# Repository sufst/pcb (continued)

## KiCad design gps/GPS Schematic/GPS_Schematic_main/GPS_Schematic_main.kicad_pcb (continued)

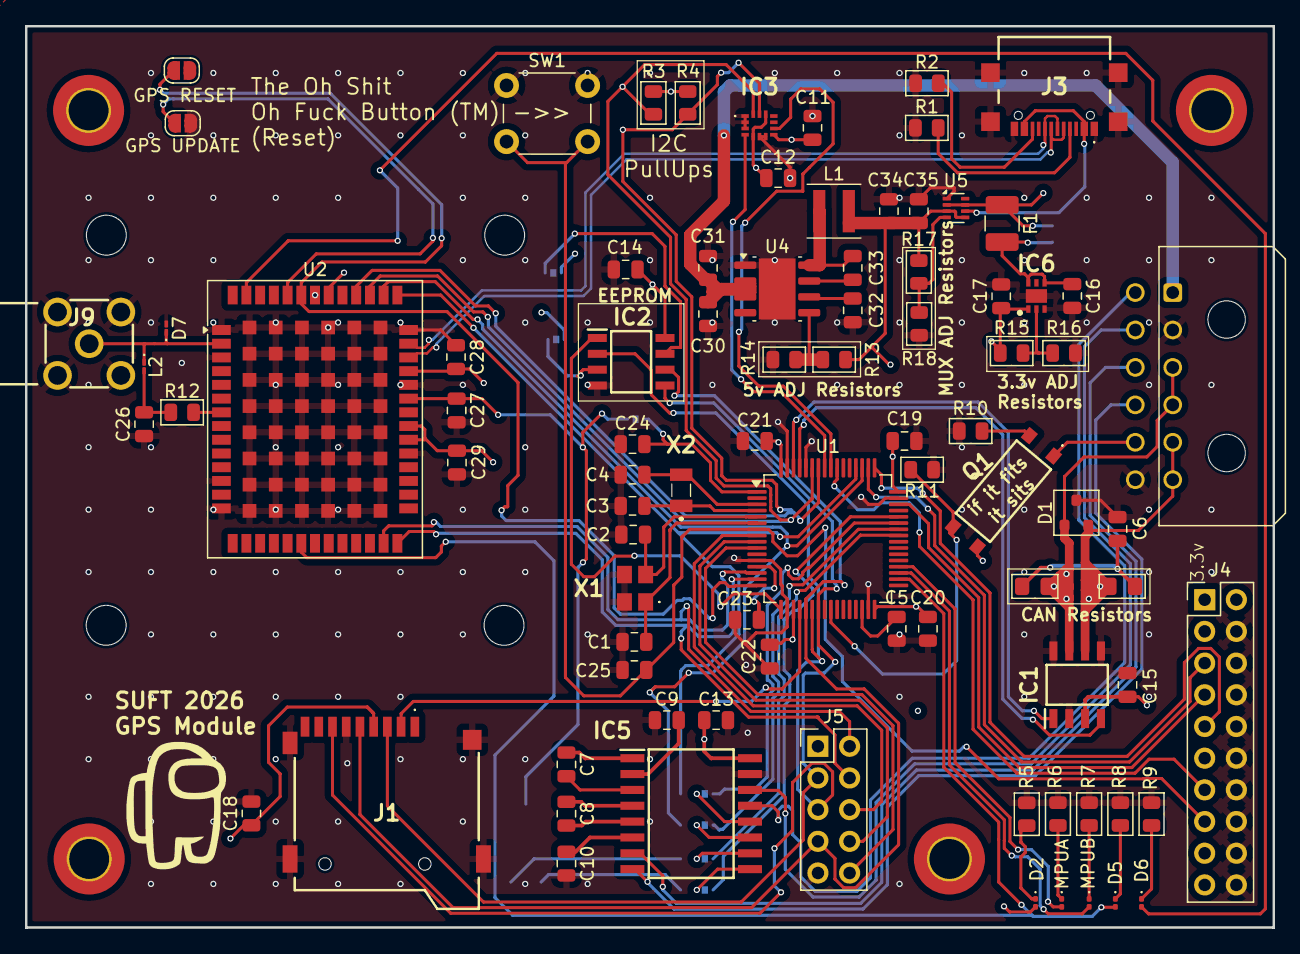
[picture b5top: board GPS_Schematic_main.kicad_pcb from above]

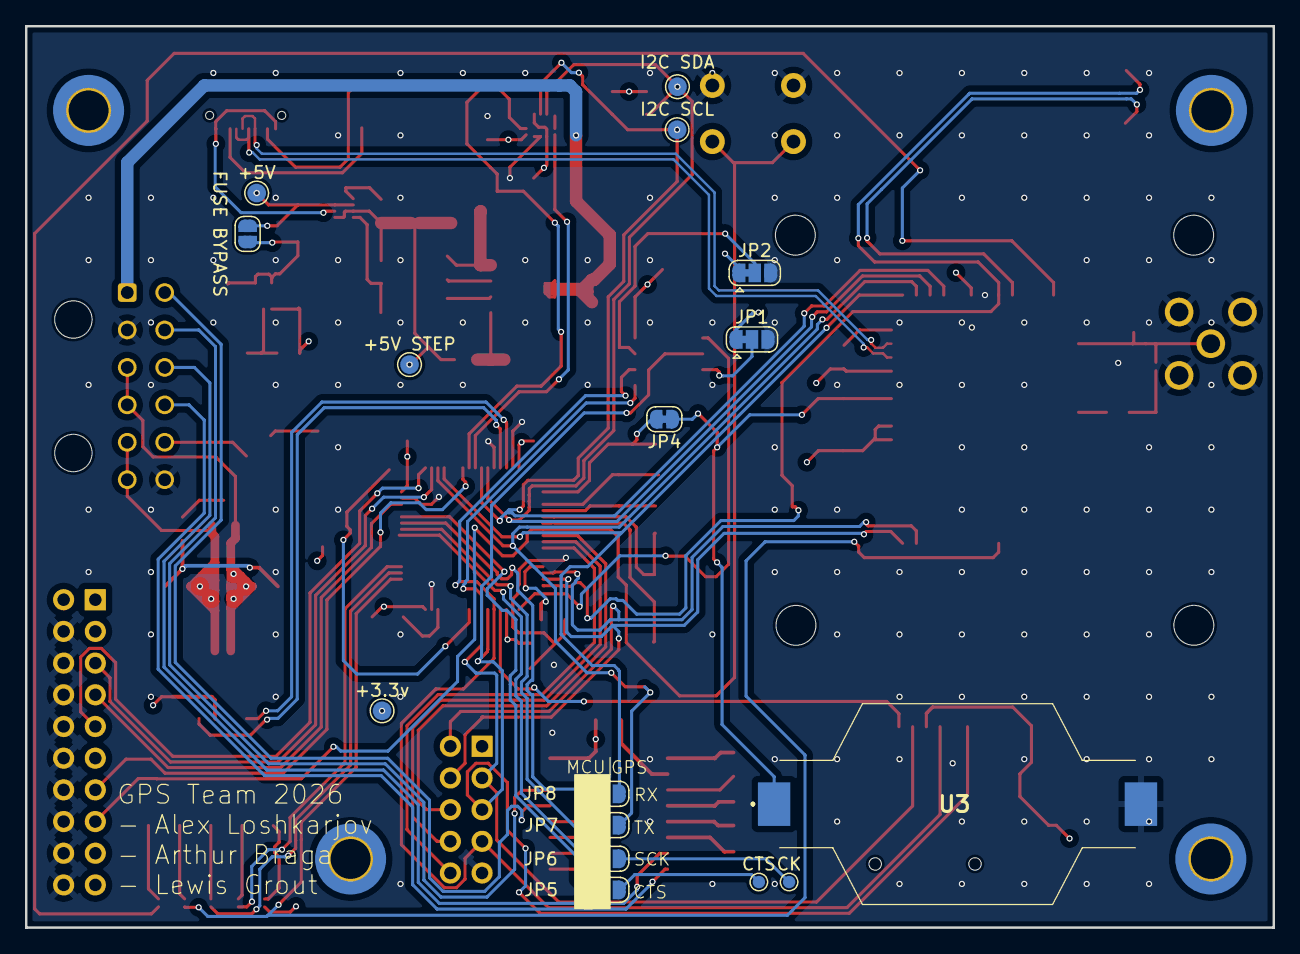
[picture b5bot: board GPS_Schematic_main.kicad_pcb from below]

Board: 4 copper layers, 100.0 x 72.2 mm, 102 parts (16 on the bottom side), 89 nets.

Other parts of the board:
+3.3v, +5V, +5V STEP: TestPoint; TestPoint_Pad_D1.5mm
CK: CK; TestPoint_Pad_D1.0mm
CTS: CTS; TestPoint_Pad_D1.0mm
FUSE BYPASS: FUSE BYPASS; SolderJumper-2_P1.3mm_Open_RoundedPad1.0x1.5mm
GPS RESET: SolderJumper_2_Open; SolderJumper-2_P1.3mm_Open_RoundedPad1.0x1.5mm
GPS UPDATE: SolderJumper_2_Open; SolderJumper-2_P1.3mm_Open_RoundedPad1.0x1.5mm
I2C SCL, I2C SDA: TestPoint; TestPoint_Pad_D1.5mm

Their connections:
+3.3V: +3.3v.1; also elsewhere on the board
+5V: +5V.1, FUSE BYPASS.1 (A); also elsewhere on the board
+5V StepDown: +5V STEP.1; also elsewhere on the board
GND: GPS UPDATE.1 (A); also elsewhere on the board
GPS_NRST: GPS RESET.2 (B); also elsewhere on the board
I2C_SCL: I2C SCL.1; also elsewhere on the board
I2C_SDA: I2C SDA.1; also elsewhere on the board
unnamed 45: GPS UPDATE.2 (B); also elsewhere on the board
unnamed 58: FUSE BYPASS.2 (B); also elsewhere on the board
unnamed 63: CTS.1; also elsewhere on the board
unnamed 64: CK.1; also elsewhere on the board

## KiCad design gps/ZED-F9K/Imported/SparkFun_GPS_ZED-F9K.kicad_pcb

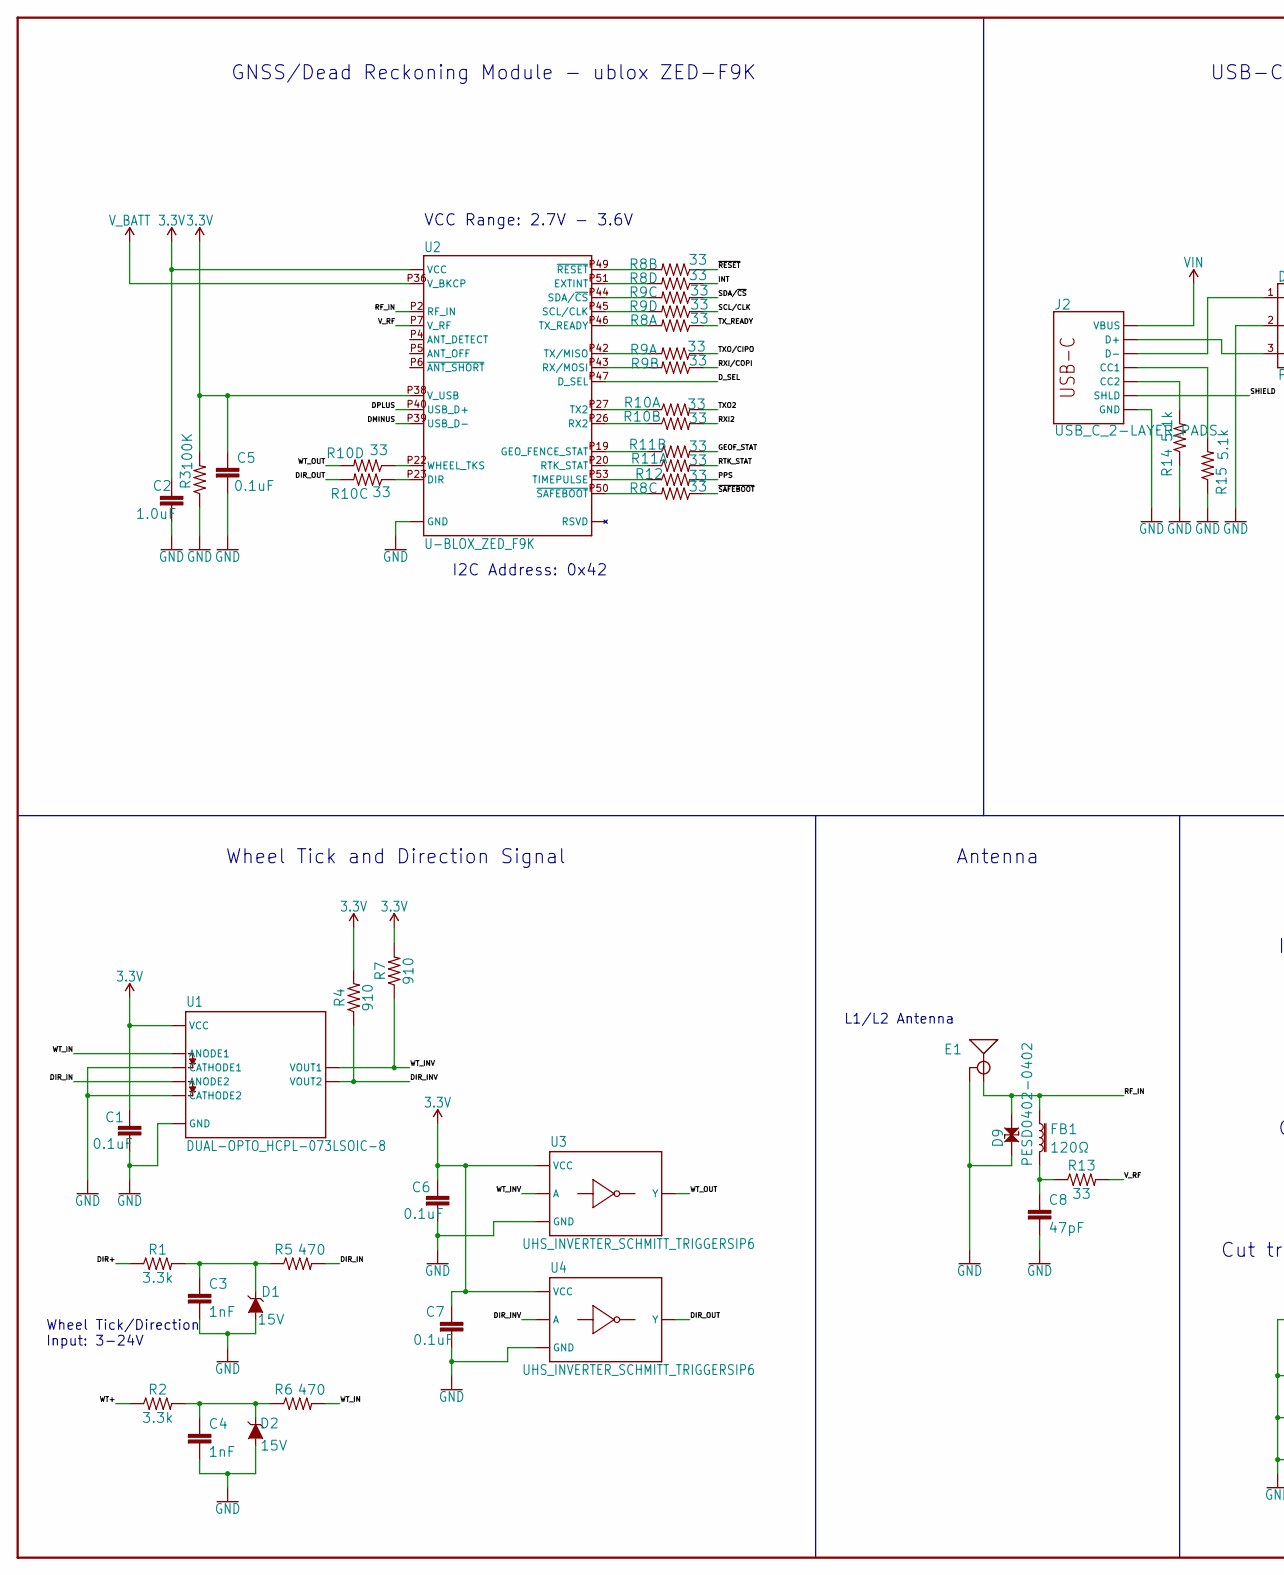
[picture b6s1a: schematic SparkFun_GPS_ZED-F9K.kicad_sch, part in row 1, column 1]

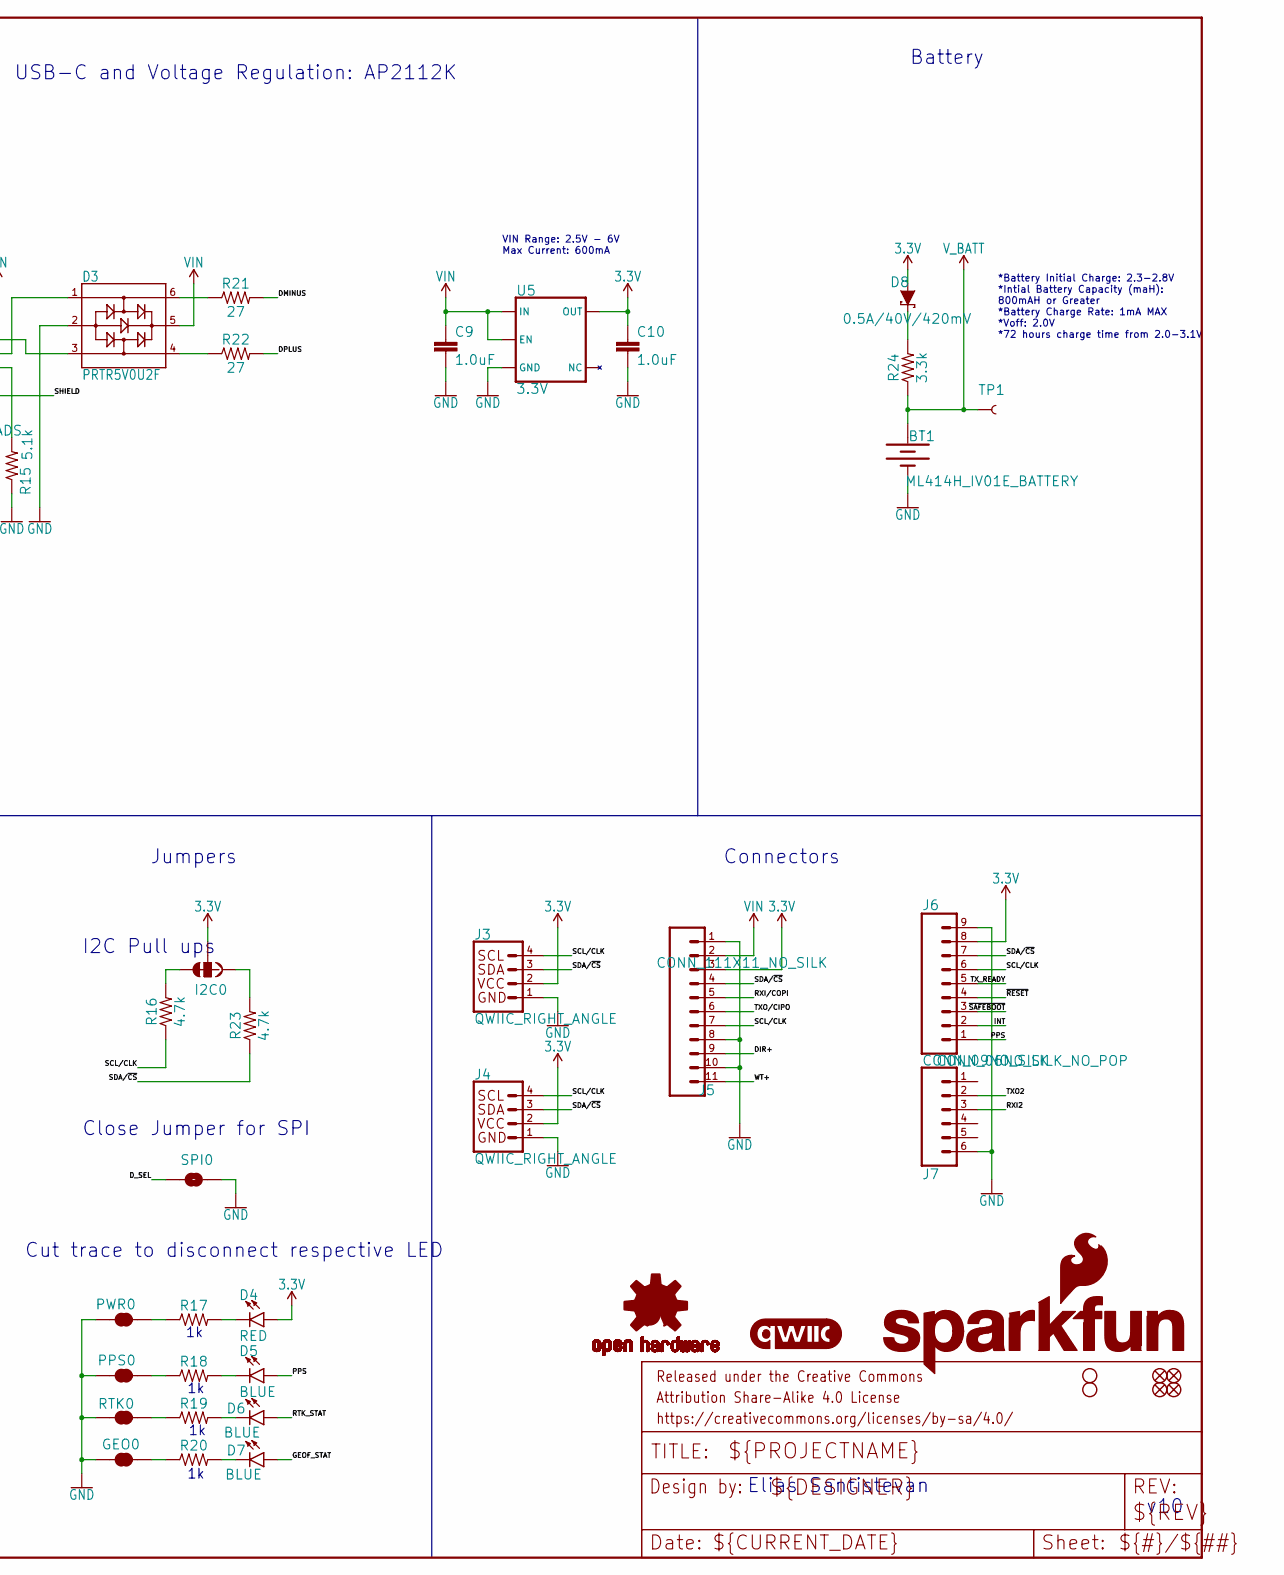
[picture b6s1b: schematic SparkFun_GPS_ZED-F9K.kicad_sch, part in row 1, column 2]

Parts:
$1_25_$_2020-03-30_22-52-05: STAND-OFFTIGHT; STAND-OFF-TIGHT
BT1: ML414H_IV01E_BATTERY; ML414H_IV01E
C1, C5, C6, C7: 0.1uF; 0402-TIGHT
C2, C9, C10: 1.0uF; 0402-TIGHT
C3, C4: 1nF; 0402
C8: 47pF; 0402
D1, D2: 15V; SOT23-3
D3: PRTR5V0U2F; SOT886
D4: RED; LED-0603
D5, D6, D7: BLUE; LED-0603
D8: 0.5A/40V/420mV; SOD-323
D9: PESD0402-0402; 0402
E1: ANTENNA-SMA-GROUNDEDEDGE_SMA; SMA-EDGE
FB1: 120Ω; 0402
FD1, FD2, FD3, FD4: FIDUCIALUFIDUCIAL; FIDUCIAL-MICRO
FRAME1: FRAME-LEDGER; CREATIVE_COMMONS
GEO0: JUMPER-SMT_2_NC_TRACE_SILK; SMT-JUMPER_2_NC_TRACE_SILK
H2: STAND-OFFTIGHT; STAND-OFF-TIGHT
I2C0: JUMPER-SMT_3_2-NC_TRACE_SILK; SMT-JUMPER_3_2-NC_TRACE_SILK
J2: USB_C_2-LAYER_PADS; USB-C-16P-2LAYER-PADS
J3, J4: QWIIC_RIGHT_ANGLE; JST04_1MM_RA
J5: CONN_111X11_NO_SILK; 1X11_NO_SILK
J6: CONN_09NO_SILK; 1X09_NO_SILK
J7: CONN_06NO_SILK_NO_POP; 1X06_NO_SILK
LOGO1: OSHW-LOGOS; OSHW-LOGO-S
LOGO2: QWIIC_LOGO_4MM; QWIIC_4MM
LOGO3: SFE_LOGO_NAME_FLAME.2_INCH; SFE_LOGO_NAME_FLAME_.2
PPS0: JUMPER-SMT_2_NC_TRACE_SILK; SMT-JUMPER_2_NC_TRACE_SILK
PWR0: JUMPER-SMT_2_NC_TRACE_SILK; SMT-JUMPER_2_NC_TRACE_SILK
R1, R2, R24: 3.3k; 0603
R3: 100K; 0402
R4, R7: 910; 0603
R5, R6: 470; 0603
R8, R9, R10, R11: 33; 1206_RA
R12, R13: 33; 0603
R14, R15: 5.1k; 0402
R16, R23: 4.7k; 0402-TIGHT
R17, R18, R19, R20: 1KOHM-0402-1/16W-1%; 0402
R21, R22: 27; 0603
RTK0: JUMPER-SMT_2_NC_TRACE_SILK; SMT-JUMPER_2_NC_TRACE_SILK
SPI0: JUMPER-SMT_2_NO_SILK; SMT-JUMPER_2_NO_SILK
TP1: TEST-POINT3X5; PAD.03X.05
U1: DUAL-OPTO_HCPL-073LSOIC-8; SO08
U2: U-BLOX_ZED_F9K; UBLOX_ZED_F9K
U3, U4: UHS_INVERTER_SCHMITT_TRIGGERSIP6; SIP6
U5: 3.3V; SOT23-5

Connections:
3.3V: C1.1, C2.1, C5.1, C6.1, C7.1, C10.1, D4.A, D8.A, I2C0.2, J3.2, J4.2, J5.3, J6.8, R3.2, R4.2, R7.2, U1.8 (VCC), U2.P33 (VCC), U2.P34 (VCC), U2.P38 (V_USB), U3.P6 (VCC), U4.P6 (VCC), U5.5 (OUT)
DIR+: J5.9, R1.1
DIR_IN: R5.2, U1.4 (ANODE2)
DIR_INV: R4.1, U1.6 (VOUT2), U4.P2 (A)
DIR_OUT: R10.P6 (2), U4.P4 (Y)
DMINUS: R21.2, U2.P39 (USB_D-)
DPLUS: R22.2, U2.P40 (USB_D+)
D_SEL: SPI0.1, U2.P47 (D_SEL)
GEOF_STAT: D7.A, R11.P7 (2)
GND: BT1.-, C1.2, C2.2, C3.2, C4.2, C5.2, C6.2, C7.2, C8.2, C9.2, C10.2, D1.1 (A), D2.1 (A), D3.2, D9.1, E1.GND@0 (GND), E1.GND@1 (GND), E1.GND@2 (GND), E1.GND@3 (GND), GEO0.1, J2.GND, J2.GND2 (GND), J3.1, J4.1, J5.1, J5.8, J5.10, J6.9, J7.6, PPS0.1, PWR0.1, R3.1, R14.1, R15.1, RTK0.1, SPI0.2, U1.2 (CATHODE1), U1.3 (CATHODE2), U1.5 (GND), U2.G1 (GND), U2.G2 (GND), U2.G3 (GND), U2.G4 (GND), U2.G5 (GND), U2.G6 (GND), U2.G7 (GND), U2.G8 (GND), U2.G9 (GND), U2.G10 (GND), U2.G11 (GND), U2.G12 (GND), U2.G13 (GND), U2.G14 (GND), U2.G15 (GND), U2.G16 (GND), U2.G17 (GND), U2.G18 (GND), U2.G19 (GND), U2.G20 (GND), U2.G21 (GND), U2.G22 (GND), U2.G23 (GND), U2.G24 (GND), U2.G25 (GND), U2.G26 (GND), U2.G27 (GND), U2.G28 (GND), U2.G29 (GND), U2.G30 (GND), U2.G31 (GND), U2.G32 (GND), U2.G33 (GND), U2.G34 (GND), U2.G35 (GND), U2.G36 (GND), U2.G37 (GND), U2.G38 (GND), U2.G39 (GND), U2.G40 (GND), U2.G41 (GND), U2.G42 (GND), U2.G43 (GND), U2.G44 (GND), U2.G45 (GND), U2.G46 (GND), U2.G47 (GND), U2.G48 (GND), U2.P1 (GND), U2.P3 (GND), U2.P12 (GND), U2.P14 (GND), U2.P32 (GND), U2.P37 (GND), U2.P41 (GND), U2.P48 (GND), U3.P3 (GND), U4.P3 (GND), U5.2 (GND)
INT: J6.2, R8.P4 (1)
unnamed: I2C0.1, R23.2
unnamed: D8.C, R24.2
unnamed: I2C0.3, R16.2
unnamed: D4.C, R17.2
unnamed: C8.1, FB1.2, R13.1
unnamed: D3.3, J2.A6 (D+), J2.B6 (D+)
unnamed: D3.1, J2.A7 (D-), J2.B7 (D-)
unnamed: PWR0.2, R17.1
unnamed: D3.6, R21.1
unnamed: D3.4, R22.1
unnamed: R8.P7 (2), U2.P49 (~RESET)
unnamed: R8.P5 (2), U2.P51 (EXTINT)
unnamed: J2.B5 (CC2), R14.2
unnamed: J2.A5 (CC1), R15.2
unnamed: R9.P6 (2), U2.P44 (SDA/~CS)
unnamed: R9.P5 (2), U2.P45 (SCL/CLK)
unnamed: R8.P8 (2), U2.P46 (TX_READY)
unnamed: R9.P8 (2), U2.P42 (TX/MISO)
unnamed: R9.P7 (2), U2.P43 (RX/MOSI)
unnamed: R10.P1 (1), U2.P27 (TX2)
unnamed: R19.1, RTK0.2
unnamed: PPS0.2, R18.1
unnamed: D5.C, R18.2
unnamed: D6.C, R19.2
unnamed: R10.P2 (1), U2.P26 (RX2)
unnamed: R11.P2 (1), U2.P19 (GEO_FENCE_STAT)
unnamed: R11.P1 (1), U2.P20 (RTK_STAT)
unnamed: R12.1, U2.P53 (TIMEPULSE)
unnamed: R8.P6 (2), U2.P50 (~SAFEBOOT)
unnamed: R10.P4 (1), U2.P22 (WHEEL_TKS)
unnamed: R10.P3 (1), U2.P23 (DIR)
unnamed: GEO0.2, R20.1
unnamed: D7.C, R20.2
unnamed: C4.1, D2.3 (C), R2.2, R6.1
unnamed: C3.1, D1.3 (C), R1.2, R5.1
PPS: D5.A, J6.1, R12.2
RF_IN: D9.2, E1.SIG (SIGNAL), FB1.1, U2.P2 (RF_IN)
RTK_STAT: D6.A, R11.P8 (2)
RXI2: J7.3, R10.P7 (2)
RXI/COPI: J5.5, R9.P2 (1)
SCL/CLK: J3.4, J4.4, J5.7, J6.6, R9.P4 (1), R16.1
SDA/~CS: J3.3, J4.3, J5.4, J6.7, R9.P3 (1), R23.1
SHIELD: J2.SHLD1 (SHLD), J2.SHLD2 (SHLD), J2.SHLD3 (SHLD), J2.SHLD4 (SHLD)
TXO2: J7.2, R10.P8 (2)
TXO/CIPO: J5.6, R9.P1 (1)
TX_READY: J6.5, R8.P1 (1)
VIN: C9.1, D3.5, J2.VBUS1 (VBUS), J2.VBUS2 (VBUS), J5.2, U5.1 (IN), U5.3 (EN)
V_BATT: BT1.+, R24.1, TP1.1, U2.P36 (V_BKCP)
V_RF: R13.2, U2.P7 (V_RF)
WT+: J5.11, R2.1
WT_IN: R6.2, U1.1 (ANODE1)
WT_INV: R7.1, U1.7 (VOUT1), U3.P2 (A)
WT_OUT: R10.P5 (2), U3.P4 (Y)
~RESET: J6.4, R8.P2 (1)
~SAFEBOOT: J6.3, R8.P3 (1)

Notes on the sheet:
USB-C and Voltage Regulation: AP2112K
Elias Santistevan
*Battery Initial Charge: 2.3-2.8V *Intial Battery Capacity (maH): 800mAH or Greater *Battery Charge Rate: 1mA MAX *Voff: 2.0V *72 hours charge time from 2.0-3.1V
Jumpers
v10
Antenna
Wheel Tick/Direction Input: 3-24V
I2C Pull ups
Cut trace to disconnect respective LED
Close Jumper for SPI
L1/L2 Antenna
Connectors
I2C Address: 0x42
VCC Range: 2.7V - 3.6V
VIN Range: 2.5V - 6V Max Current: 600mA
Battery
Wheel Tick and Direction Signal
GNSS/Dead Reckoning Module - ublox ZED-F9K

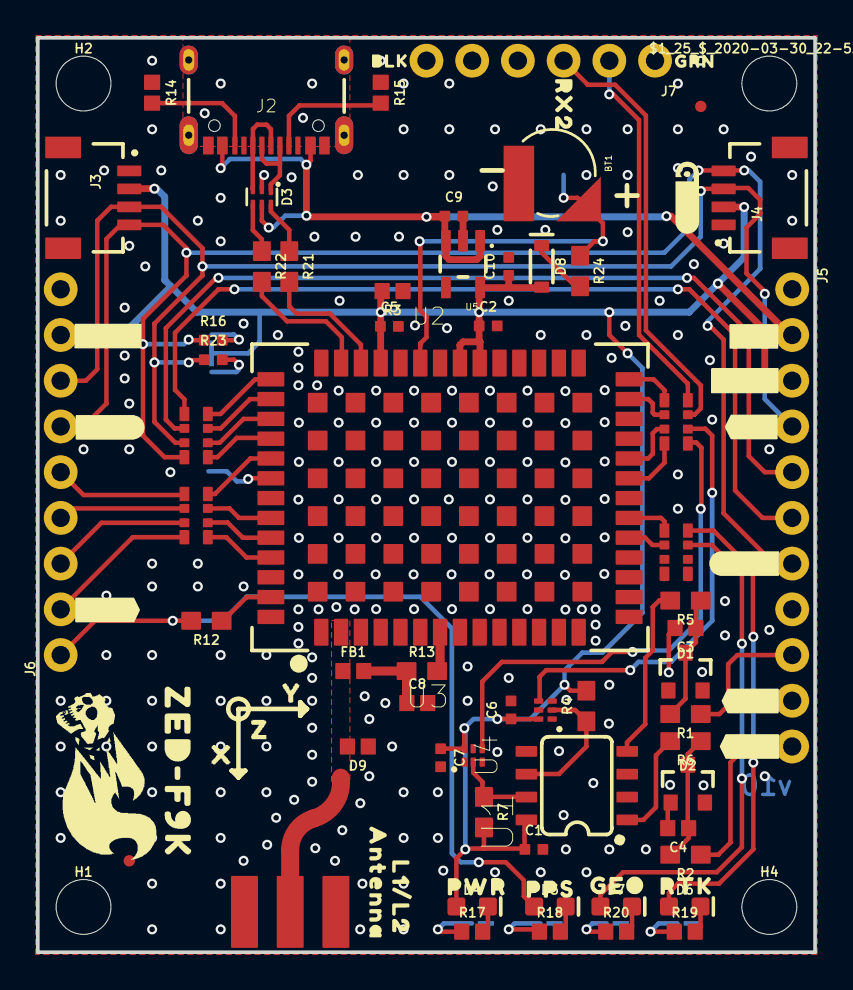
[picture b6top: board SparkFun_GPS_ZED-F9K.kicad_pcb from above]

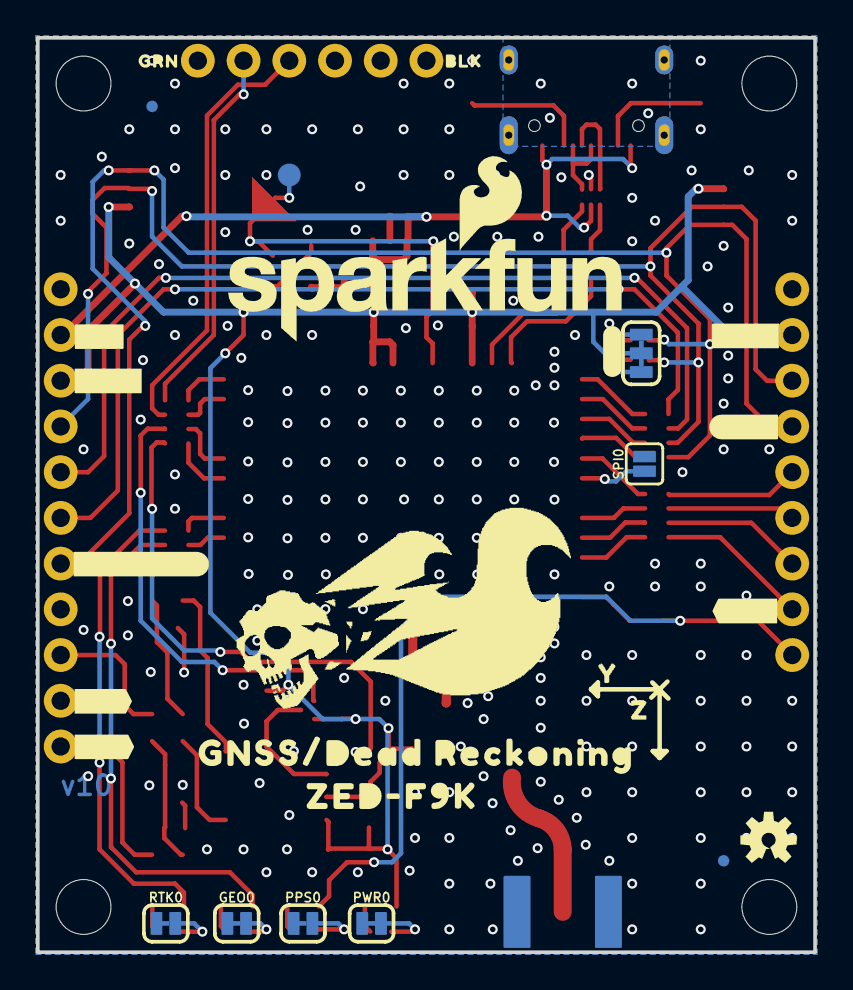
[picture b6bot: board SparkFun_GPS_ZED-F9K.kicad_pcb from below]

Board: 2 copper layers, 43.2 x 50.8 mm, 149 parts (47 on the bottom side), 66 nets.

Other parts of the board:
H1, H4: STAND-OFFTIGHT; STAND-OFF-TIGHT
U$1: PWR22
U$2: PPS21
U$3: GEO23
U$4: RTK24
U$5: #W##16
U$6: #W##15
U$7, U$14, U$22, U$37, U$55: #3V3#6
U$8: #D##13
U$9: #D##14
U$10: #SCK#12
U$11: #CIPO#10
U$12: #COPI#9
U$13: ##CS##11
U$15, U$24: #5V#1
U$16, U$17, U$25, U$36, U$44, U$58: #GND#0
U$18: #TXO2#20
U$19, U$20: DEAD#RECKONING#GPS#BOARD#SILK#FINAL#JPG
U$21: RX224
U$23: BLK225
U$26: GRN226
U$27: #SDA##CS##10
U$28: #RXI#COPI#8
U$30: #SCL#SCK#12
U$31: #D##6
U$32: X1
U$33: #D##7
U$34: #W##4
U$35: #W##5
U$38: #SDA#6
U$39: #SCL#7
U$40: #TXR#3
U$41: ##RST##16
U$42: ##SFBT##17
U$43: #INT#8
U$45: #PPS#0
U$46: #RTK#25
U$47: #GEO#24
U$48: #PPS#21
U$49: L1#L2229
U$50, U$52: Y2
U$51: #PWR#23
U$53: #SPI#22
U$54: #I2C#23
U$56: #SDA#12
U$57, U$63: Z0
U$59: #RXI2#227
U$60: #TXO2#1
U$61: BLK227
U$62: ANTENNA229
U$64: GRN228
U$65: GNSS#DEAD_RECKONING230
U$66: #SCL#13
U$67: #TXR#19
U$68: ##RST##17
U$69: ##SFBT##18
U$70: #INT#14
U$71: #PPS#20
U$72, U$73: ZED#F9K230
U$74: #TXO#CIPO#9

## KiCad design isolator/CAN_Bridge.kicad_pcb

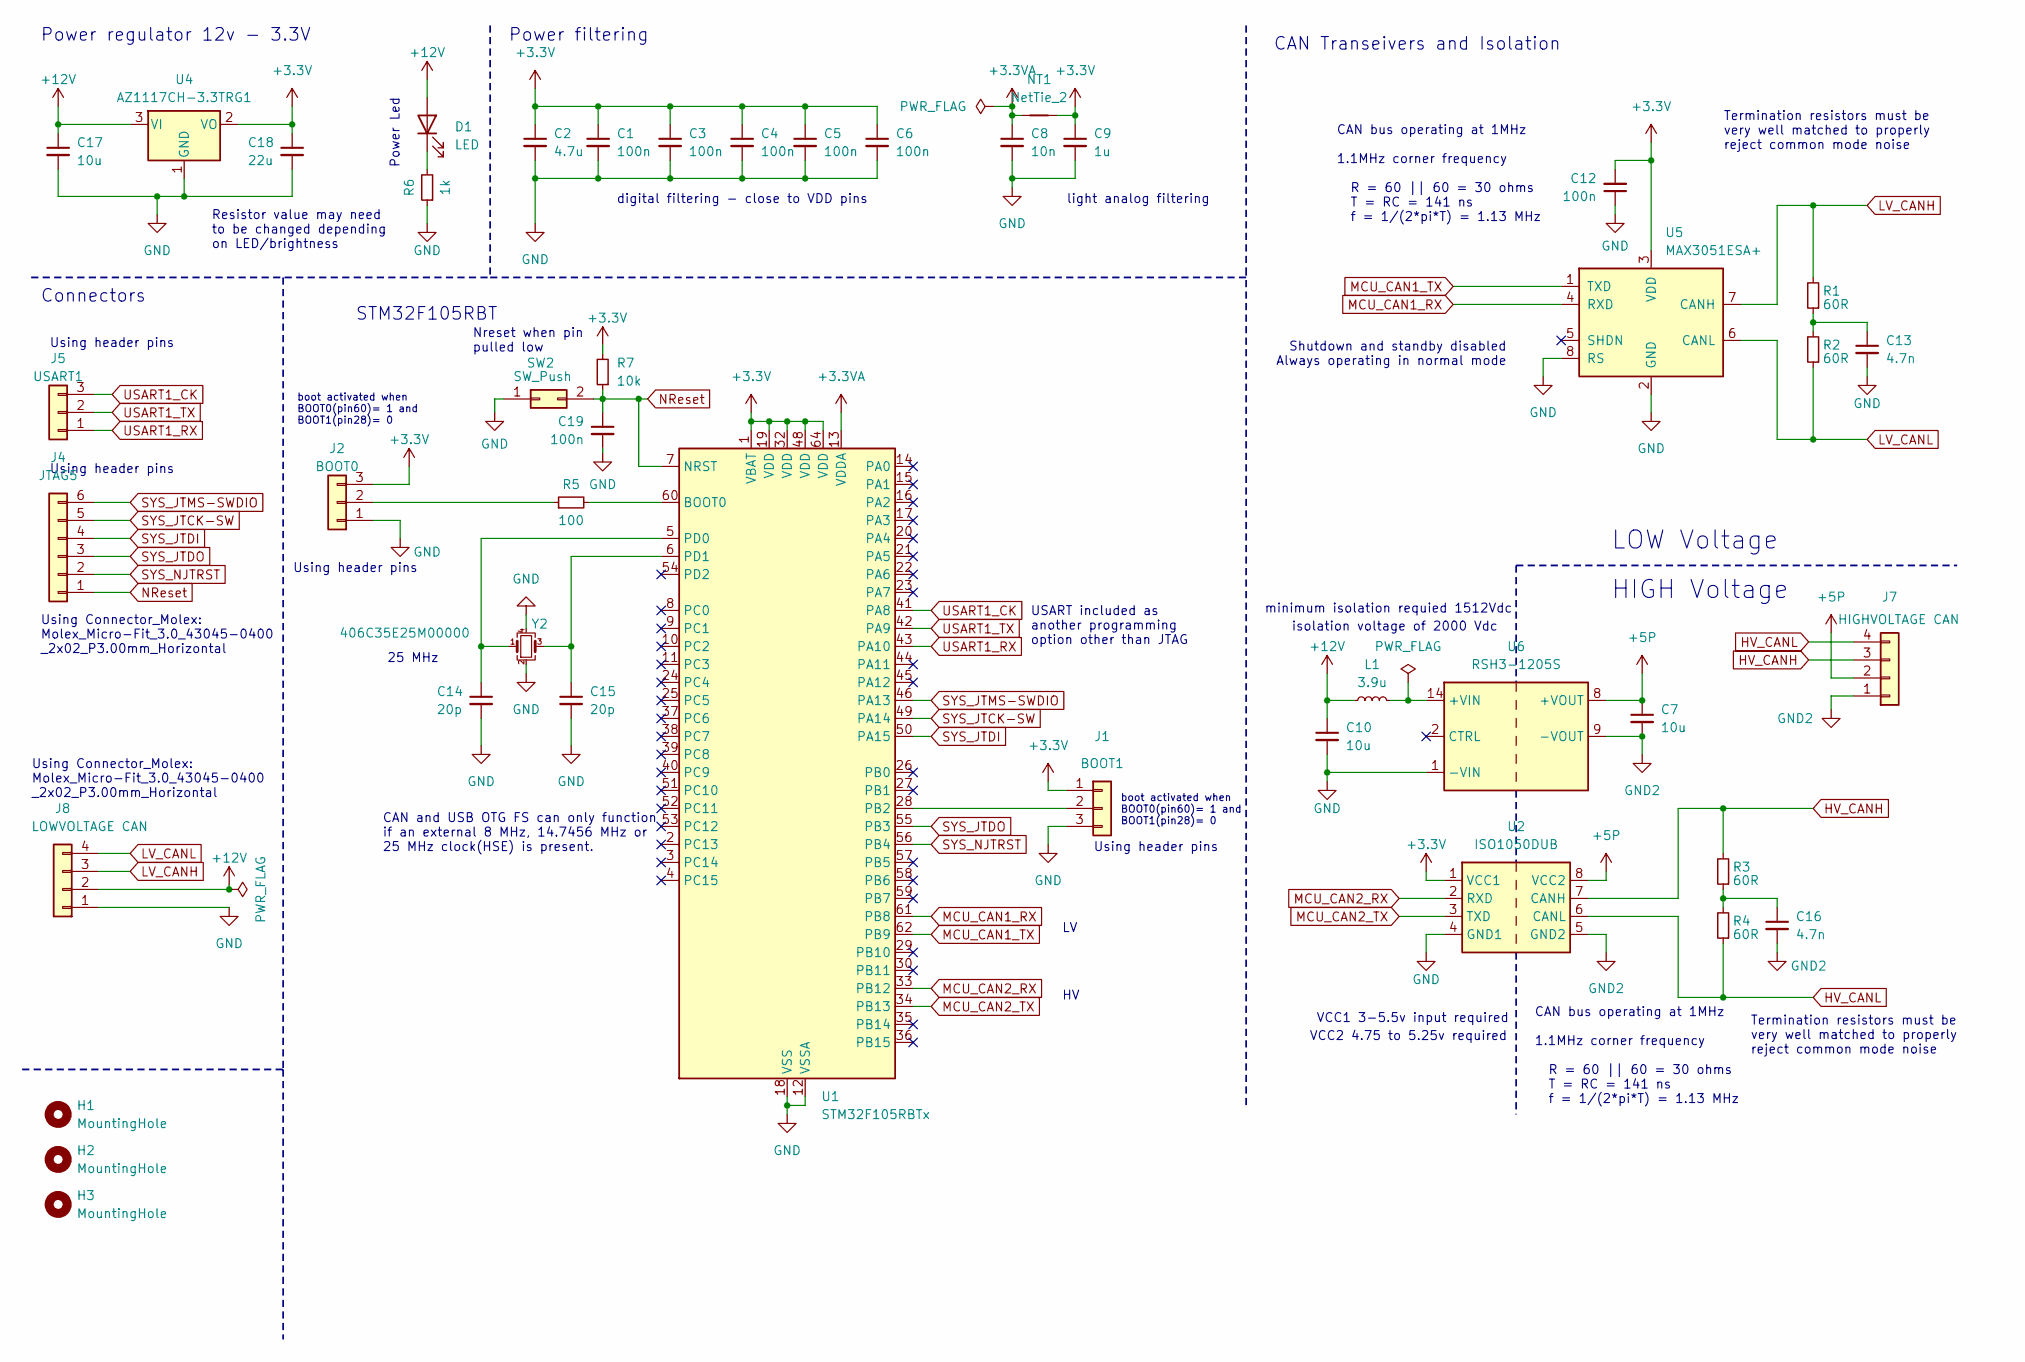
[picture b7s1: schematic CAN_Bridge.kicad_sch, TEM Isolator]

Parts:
C1, C3, C4, C5, C6, C12, C19: 100n; C_0805_2012Metric_Pad1.18x1.45mm_HandSolder
C2: 4.7u; C_1206_3216Metric_Pad1.33x1.80mm_HandSolder
C7, C10: 10u; C_0805_2012Metric_Pad1.18x1.45mm_HandSolder
C8: 10n; C_0805_2012Metric_Pad1.18x1.45mm_HandSolder
C9: 1u; C_0805_2012Metric_Pad1.18x1.45mm_HandSolder
C13, C16: 4.7n; C_0805_2012Metric_Pad1.18x1.45mm_HandSolder
C14, C15: 20p; C_0805_2012Metric_Pad1.18x1.45mm_HandSolder
C17: 10u; C_1206_3216Metric_Pad1.33x1.80mm_HandSolder
C18: 22u; C_1206_3216Metric_Pad1.33x1.80mm_HandSolder
D1: LED; LED_0805_2012Metric_Pad1.15x1.40mm_HandSolder
H1, H2, H3: MountingHole; MountingHole_4.3mm_M4
J1: BOOT1; PinHeader_1x03_P2.54mm_Vertical
J2: BOOT0; PinHeader_1x03_P2.54mm_Vertical
J4: JTAG5; PinHeader_1x06_P2.54mm_Vertical
J5: USART1; PinHeader_1x03_P2.54mm_Vertical
J7: HIGHVOLTAGE CAN; Molex_Micro-Fit_3.0_43045-0400_2x02_P3.00mm_Horizontal
J8: LOWVOLTAGE CAN; Molex_Micro-Fit_3.0_43045-0400_2x02_P3.00mm_Horizontal
L1: 3.9u; RLS-397
NT1: NetTie_2; NetTie-2_SMD_Pad0.5mm
R1, R2, R3, R4: 60R; R_0805_2012Metric_Pad1.20x1.40mm_HandSolder
R5: 100; R_0805_2012Metric_Pad1.20x1.40mm_HandSolder
R6: 1k; R_0805_2012Metric_Pad1.20x1.40mm_HandSolder
R7: 10k; R_0805_2012Metric_Pad1.20x1.40mm_HandSolder
SW2: SW_Push; PinHeader_1x02_P2.54mm_Vertical
U1: STM32F105RBTx; LQFP-64_10x10mm_P0.5mm
U2: ISO1050DUB; SOP-8_6.62x9.15mm_P2.54mm
U4: AZ1117CH-3.3TRG1; SOT-223-3_TabPin2
U5: MAX3051ESA+; SOIC-8_3.9x4.9mm_P1.27mm
U6: RSH3-1205S; SMDIP-14_15.5mm
Y2: 406C35E25M00000; Crystal_SMD_0603-4Pin_6.0x3.5mm_HandSoldering

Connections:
+3.3V: C1.1, C2.1, C3.1, C4.1, C5.1, C6.1, C9.1, C12.2, C18.1, J1.1, J2.3, NT1.2, R7.2, U1.1 (VBAT), U1.19 (VDD), U1.32 (VDD), U1.48 (VDD), U1.64 (VDD), U2.1 (VCC1), U4.2 (VO), U5.3 (VDD)
+3.3VA: C8.1, NT1.1, U1.13 (VDDA)
+5P: C7.1, J7.2, U2.8 (VCC2), U6.8 (+VOUT)
+12V: C10.1, C17.1, D1.2 (A), J8.2, L1.1, U4.3 (VI)
GND: C1.2, C2.2, C3.2, C4.2, C5.2, C6.2, C8.2, C9.2, C10.2, C12.1, C13.2, C14.2, C15.2, C17.2, C18.2, C19.2, J1.3, J2.1, J8.1, R6.1, SW2.1, U1.12 (VSSA), U1.18 (VSS), U1.31 (VSS), U1.47 (VSS), U1.63 (VSS), U2.4 (GND1), U4.1 (GND), U5.2 (GND), U5.8 (RS), U6.1 (-VIN), Y2.2, Y2.4
GND2: C7.2, C16.2, J7.1, U2.5 (GND2), U6.9 (-VOUT)
HV_CANH: J7.3, R3.2, U2.7 (CANH)
HV_CANL: J7.4, R4.1, U2.6 (CANL)
LV_CANH: J8.3, R1.2, U5.7 (CANH)
LV_CANL: J8.4, R2.1, U5.6 (CANL)
MCU_CAN1_RX: U1.61 (PB8), U5.4 (RXD)
MCU_CAN1_TX: U1.62 (PB9), U5.1 (TXD)
MCU_CAN2_RX: U1.33 (PB12), U2.2 (RXD)
MCU_CAN2_TX: U1.34 (PB13), U2.3 (TXD)
NReset: C19.1, J4.1, R7.1, SW2.2, U1.7 (NRST)
unnamed: C13.1, R1.1, R2.2
unnamed: C16.1, R3.1, R4.2
unnamed: D1.1 (K), R6.2
unnamed: J1.2, U1.28 (PB2)
unnamed: J2.2, R5.1
unnamed: R5.2, U1.60 (BOOT0)
unnamed: C14.1, U1.5 (PD0), Y2.1
unnamed: C15.1, U1.6 (PD1), Y2.3
unnamed: L1.2, U6.14 (+VIN)
SYS_JTCK-SW: J4.5, U1.49 (PA14)
SYS_JTDI: J4.4, U1.50 (PA15)
SYS_JTDO: J4.3, U1.55 (PB3)
SYS_JTMS-SWDIO: J4.6, U1.46 (PA13)
SYS_NJTRST: J4.2, U1.56 (PB4)
USART1_CK: J5.3, U1.41 (PA8)
USART1_RX: J5.1, U1.43 (PA10)
USART1_TX: J5.2, U1.42 (PA9)

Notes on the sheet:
CAN and USB OTG FS can only function if an external 8 MHz, 14.7456 MHz or 25 MHz clock(HSE) is present.
CAN bus operating at 1MHz 1.1MHz corner frequency R = 60 || 60 = 30 ohms T = RC = 141 ns f = 1/(2*pi*T) = 1.13 MHz
Using header pins
USART included as another programming option other than JTAG
isolation voltage of 2000 Vdc
STM32F105RBT
minimum isolation requied 1512Vdc
digital filtering - close to VDD pins
boot activated when BOOT0(pin60)= 1 and BOOT1(pin28)= 0
Power regulator 12v - 3.3V
light analog filtering
VCC2 4.75 to 5.25v required
Nreset when pin pulled low
Power Led
Connectors
CAN Transeivers and Isolation
25 MHz
Shutdown and standby disabled Always operating in normal mode
LOW Voltage
Power filtering
Termination resistors must be very well matched to properly reject common mode noise
Using Connector_Molex: Molex_Micro-Fit_3.0_43045-0400 _2x02_P3.00mm_Horizontal
HIGH Voltage
Resistor value may need to be changed depending on LED/brightness
VCC1 3-5.5v input required

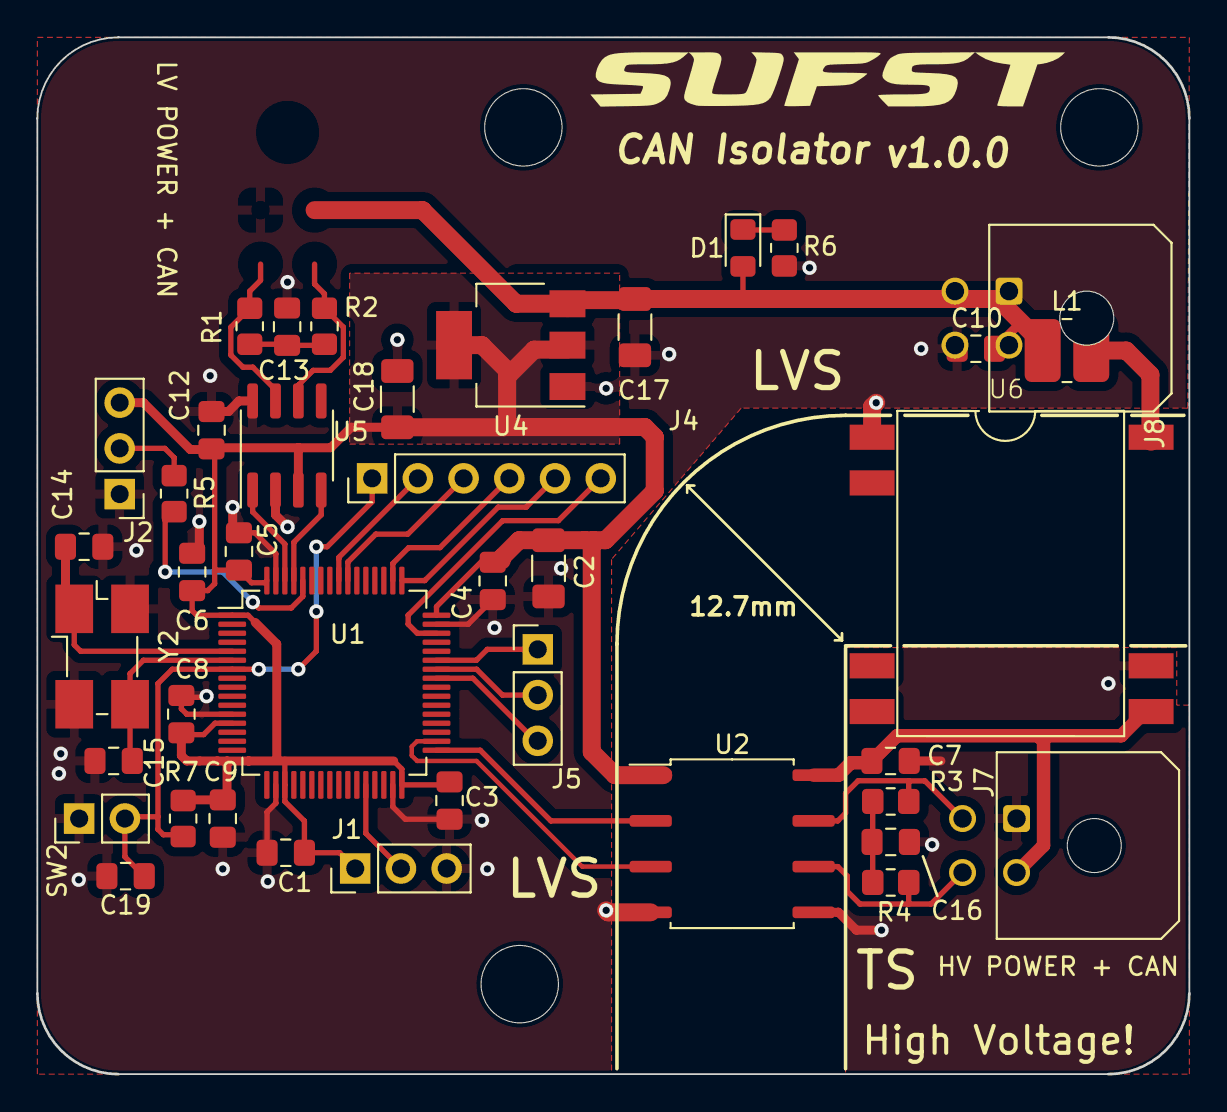
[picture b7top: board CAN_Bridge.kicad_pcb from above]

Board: 2 copper layers, 64.0 x 57.6 mm, 44 parts (0 on the bottom side), 32 nets.
